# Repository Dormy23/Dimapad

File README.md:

# Dimapad

## Description

Dimapad is An elegant 3x2 macropad with rotary encoder and OLED display

## Pinout

| Device |    |
|--------|------|
| **Matrix rows** | GPIO28, GPIO0, GPIO3 |
| **Matrix cols** | GPIO4, GPIO2, GPIO1 |
| **Encoder** | GPIO26, GPIO27 |
| **OLED** (I2C) | SDA: GPIO6, SCL: GPIO7 |
| **RGB LED** | GPIO29 |

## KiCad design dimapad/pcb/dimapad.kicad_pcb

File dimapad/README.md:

# Dimapad

## Description

Dimapad is An elegant 3x2 macropad with rotary encoder and OLED display

## Pinout

| Device |    |
|--------|------|
| **Matrix rows** | GPIO28, GPIO0, GPIO3 |
| **Matrix cols** | GPIO4, GPIO2, GPIO1 |
| **Encoder** | GPIO26, GPIO27 |
| **OLED** (I2C) | SDA: GPIO6, SCL: GPIO7 |
| **RGB LED** | GPIO29 |

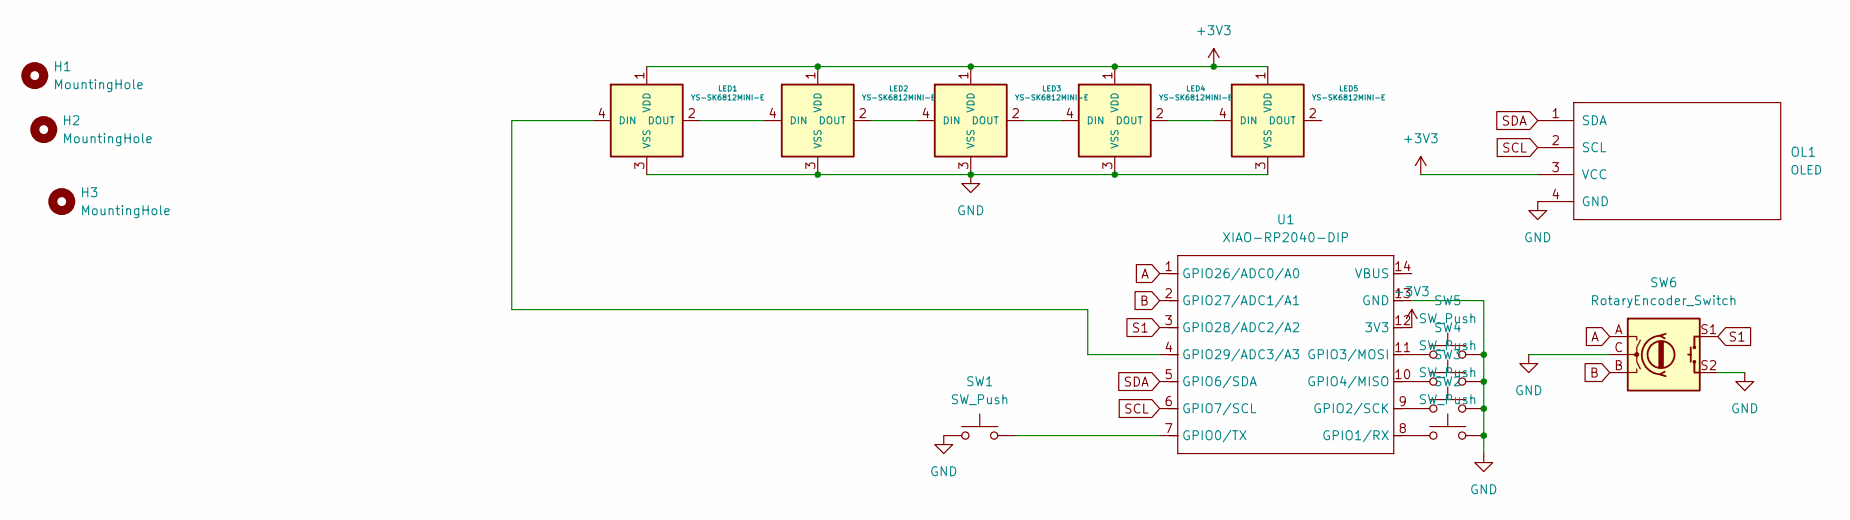
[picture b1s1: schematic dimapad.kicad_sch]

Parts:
H1, H2, H3: MountingHole; MountingHole_3.2mm_M3
LED1, LED2, LED3, LED4, LED5: YS-SK6812MINI-E; MX_SK6812MINI-E_REV
OL1: OLED
SW1, SW2, SW3, SW4, SW5: SW_Push; SW_Cherry_MX_1.00u_PCB
SW6: RotaryEncoder_Switch; RotaryEncoder_Alps_EC11E-Switch_Vertical_H20mm
U1: XIAO-RP2040-DIP

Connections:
+3V3: LED1.1 (VDD), LED2.1 (VDD), LED3.1 (VDD), LED4.1 (VDD), LED5.1 (VDD), OL1.3 (VCC), U1.12 (3V3)
A: SW6.A, U1.1 (GPIO26/ADC0/A0)
B: SW6.B, U1.2 (GPIO27/ADC1/A1)
GND: LED1.3 (VSS), LED2.3 (VSS), LED3.3 (VSS), LED4.3 (VSS), LED5.3 (VSS), OL1.4 (GND), SW1.1, SW2.2, SW3.2, SW4.2, SW5.2, SW6.C, SW6.S2, U1.13 (GND)
unnamed: LED1.4 (DIN), U1.4 (GPIO29/ADC3/A3)
unnamed: LED1.2 (DOUT), LED2.4 (DIN)
unnamed: LED2.2 (DOUT), LED3.4 (DIN)
unnamed: LED3.2 (DOUT), LED4.4 (DIN)
unnamed: LED4.2 (DOUT), LED5.4 (DIN)
unnamed: SW1.2, U1.7 (GPIO0/TX)
unnamed: SW2.1, U1.8 (GPIO1/RX)
unnamed: SW3.1, U1.9 (GPIO2/SCK)
unnamed: SW5.1, U1.11 (GPIO3/MOSI)
unnamed: SW4.1, U1.10 (GPIO4/MISO)
S1: SW6.S1, U1.3 (GPIO28/ADC2/A2)
SCL: OL1.2 (SCL), U1.6 (GPIO7/SCL)
SDA: OL1.1 (SDA), U1.5 (GPIO6/SDA)

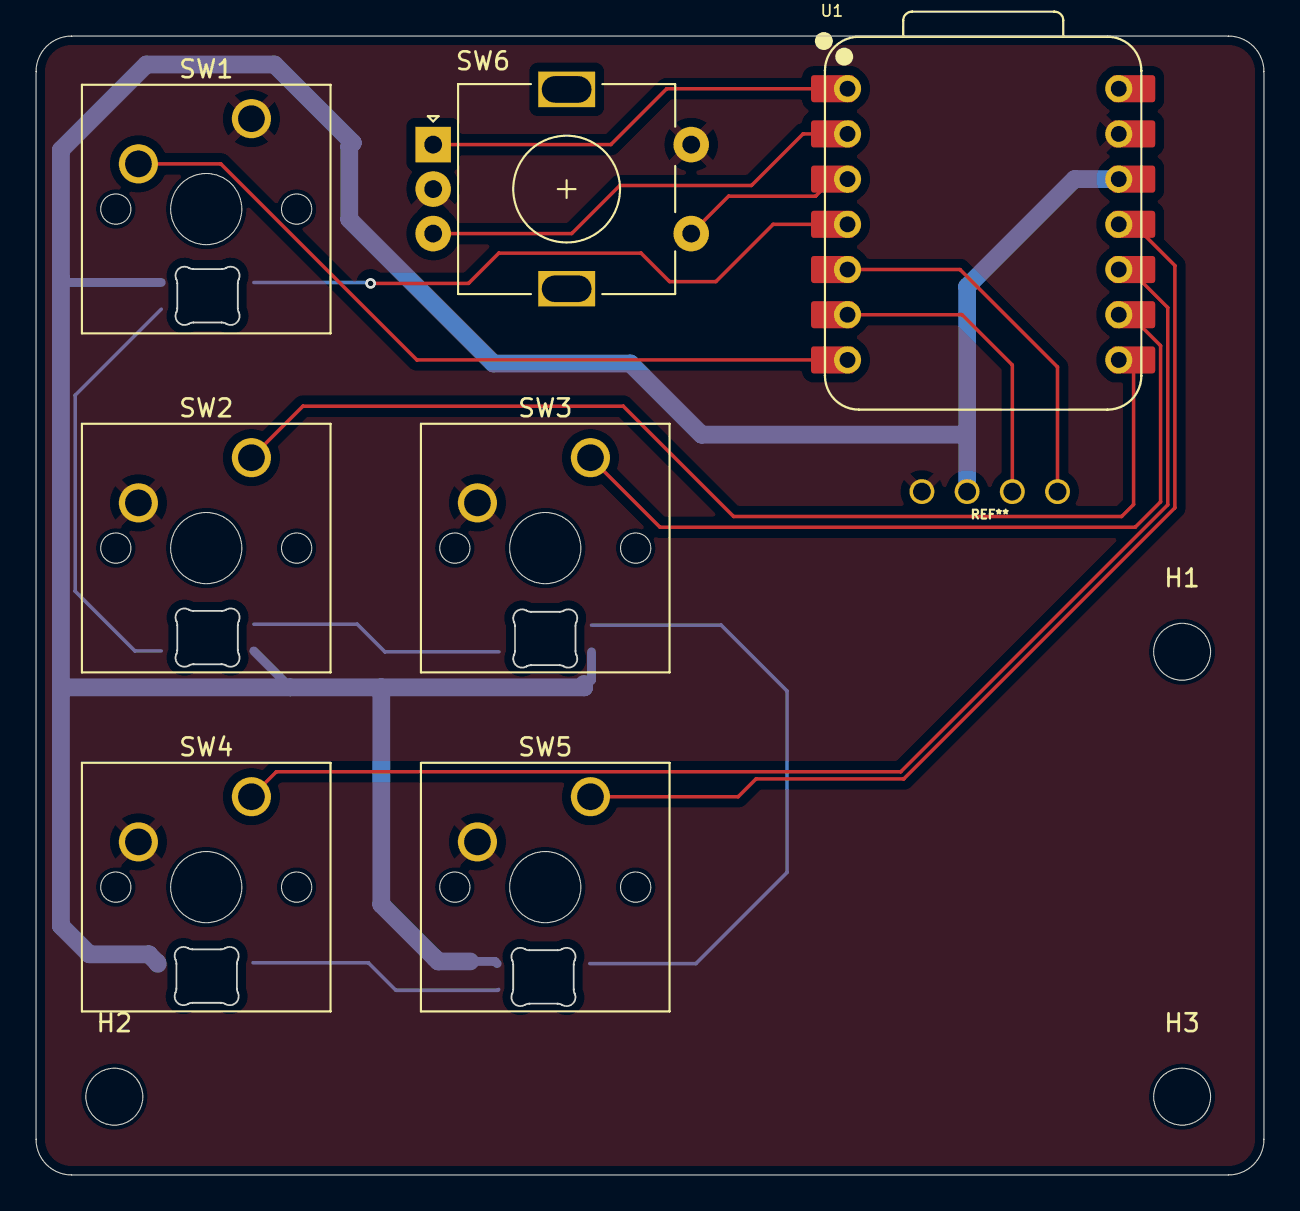
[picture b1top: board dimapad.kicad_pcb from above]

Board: 2 copper layers, 69.0 x 64.0 mm, 16 parts (0 on the bottom side), 17 nets.

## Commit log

2025-12-23 daje roma
2025-12-25 images of pcb and the schematic
2025-12-26 I hope Tanook likes it <3
